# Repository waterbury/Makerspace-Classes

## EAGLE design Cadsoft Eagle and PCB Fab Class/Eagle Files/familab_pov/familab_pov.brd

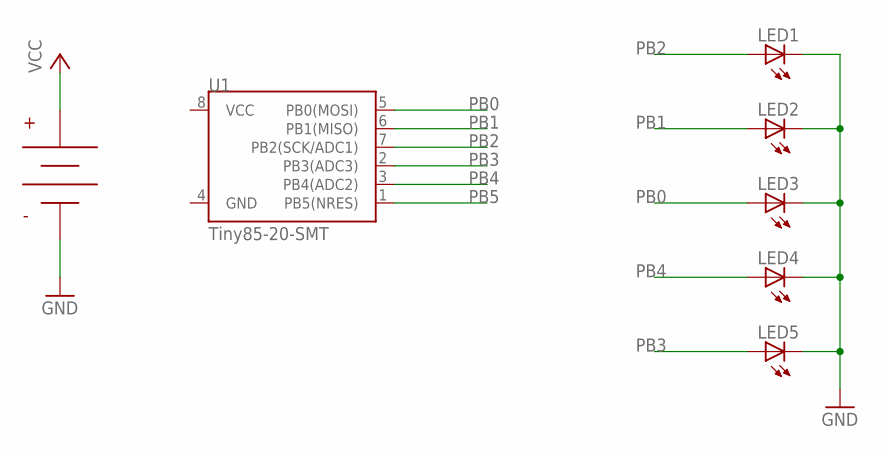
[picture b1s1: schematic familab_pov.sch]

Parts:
LED1, LED2, LED3, LED4, LED5: LED; LED5MM_SMD_SIDE
U1: Tiny85-20-SMT; SO08-EIAJ
U$1: CR2032_HOLDER; CR2032_BC2032-F1

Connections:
GND: LED1.C, LED2.C, LED3.C, LED4.C, LED5.C, U$1.NEG
PB0: LED3.A, U1.5 (PB0(MOSI))
PB1: LED2.A, U1.6 (PB1(MISO))
PB2: LED1.A, U1.7 (PB2(SCK/ADC1))
PB3: LED5.A, U1.2 (PB3(ADC3))
PB4: LED4.A, U1.3 (PB4(ADC2))
PB5: U1.1 (PB5(NRES))
VCC: U$1.POS

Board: 2 copper layers, 7 parts (0 on the bottom side), 6 nets, no tracks yet.

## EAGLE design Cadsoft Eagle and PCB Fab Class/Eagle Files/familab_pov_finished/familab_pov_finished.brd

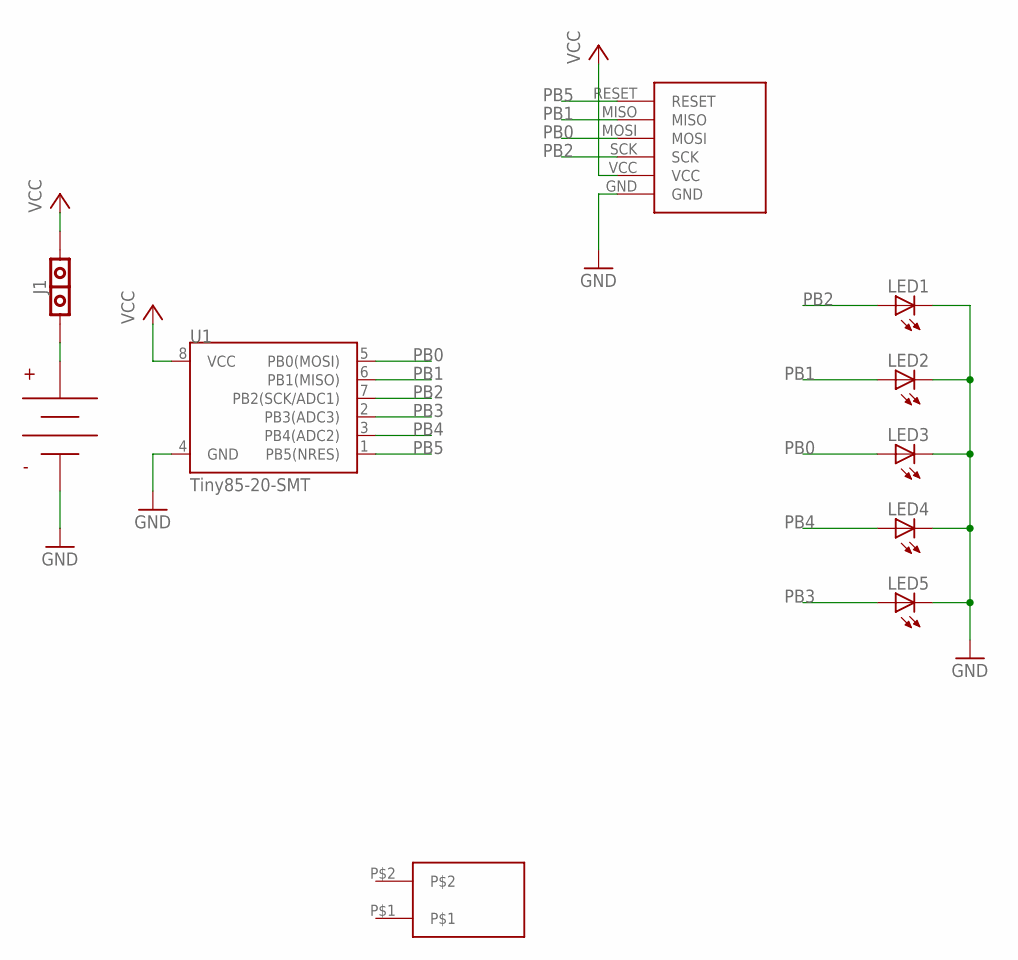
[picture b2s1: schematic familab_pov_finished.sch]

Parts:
J1: JUMPERSIDE; JUMPER_SMD_SIDE
LED1, LED2, LED3, LED4, LED5: LEDLED_5MM_SMD_SIDE; LED5MM_SMD_SIDE
U1: Tiny85-20-SMT; SO08-EIAJ
U$1: CR2032_HOLDER; CR2032_BC2032-F1
U$2: MOUNTING_PAD; MOUNTING_PADS
U$4: ICSP_PROGRAM; POV_ISP_CONNECTOR

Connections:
GND: LED1.CATHODE (C), LED2.CATHODE (C), LED3.CATHODE (C), LED4.CATHODE (C), LED5.CATHODE (C), U1.4 (GND), U$1.NEG, U$4.GND
unnamed: J1.P$1, U$1.POS
PB0: LED3.ANODE (A), U1.5 (PB0(MOSI)), U$4.MOSI
PB1: LED2.ANODE (A), U1.6 (PB1(MISO)), U$4.MISO
PB2: LED1.ANODE (A), U1.7 (PB2(SCK/ADC1)), U$4.SCK
PB3: LED5.ANODE (A), U1.2 (PB3(ADC3))
PB4: LED4.ANODE (A), U1.3 (PB4(ADC2))
PB5: U1.1 (PB5(NRES)), U$4.RESET
VCC: J1.P$2, U1.8 (VCC), U$4.VCC

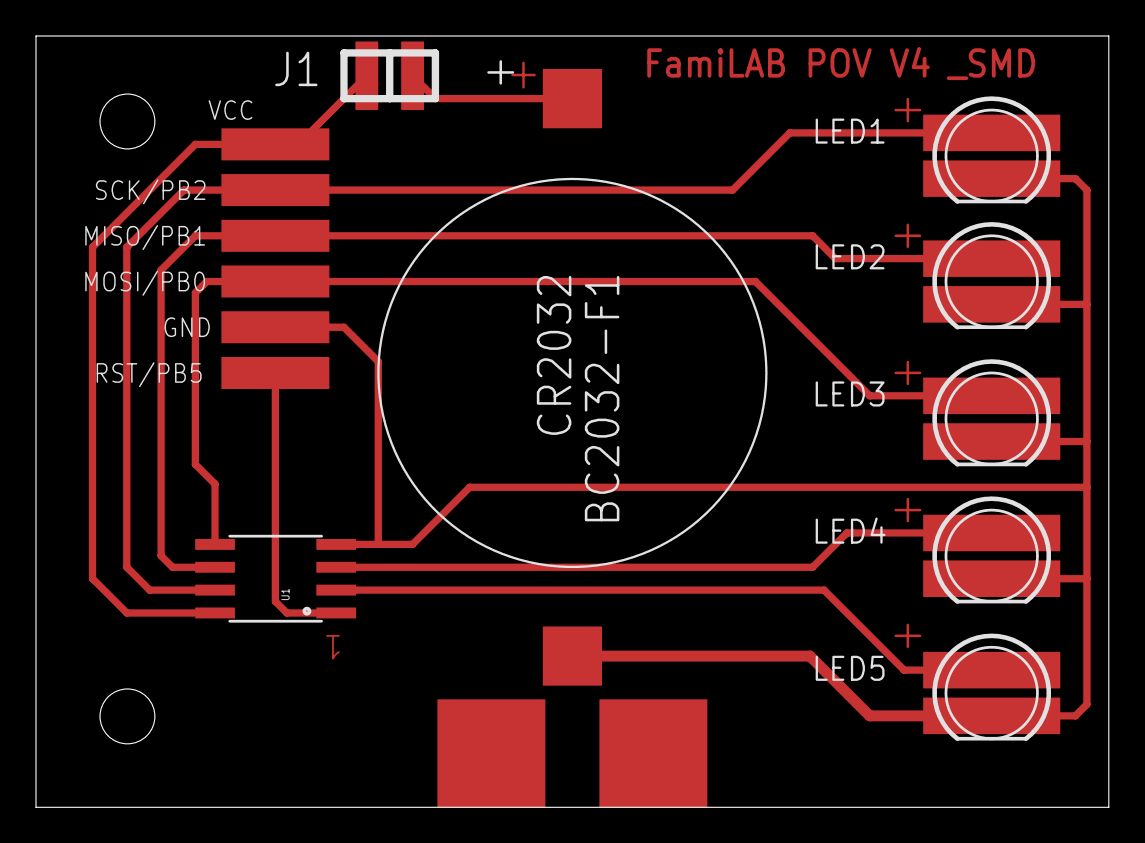
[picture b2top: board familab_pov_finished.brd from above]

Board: 2 copper layers, 59.6 x 42.9 mm, 10 parts (0 on the bottom side), 9 nets.

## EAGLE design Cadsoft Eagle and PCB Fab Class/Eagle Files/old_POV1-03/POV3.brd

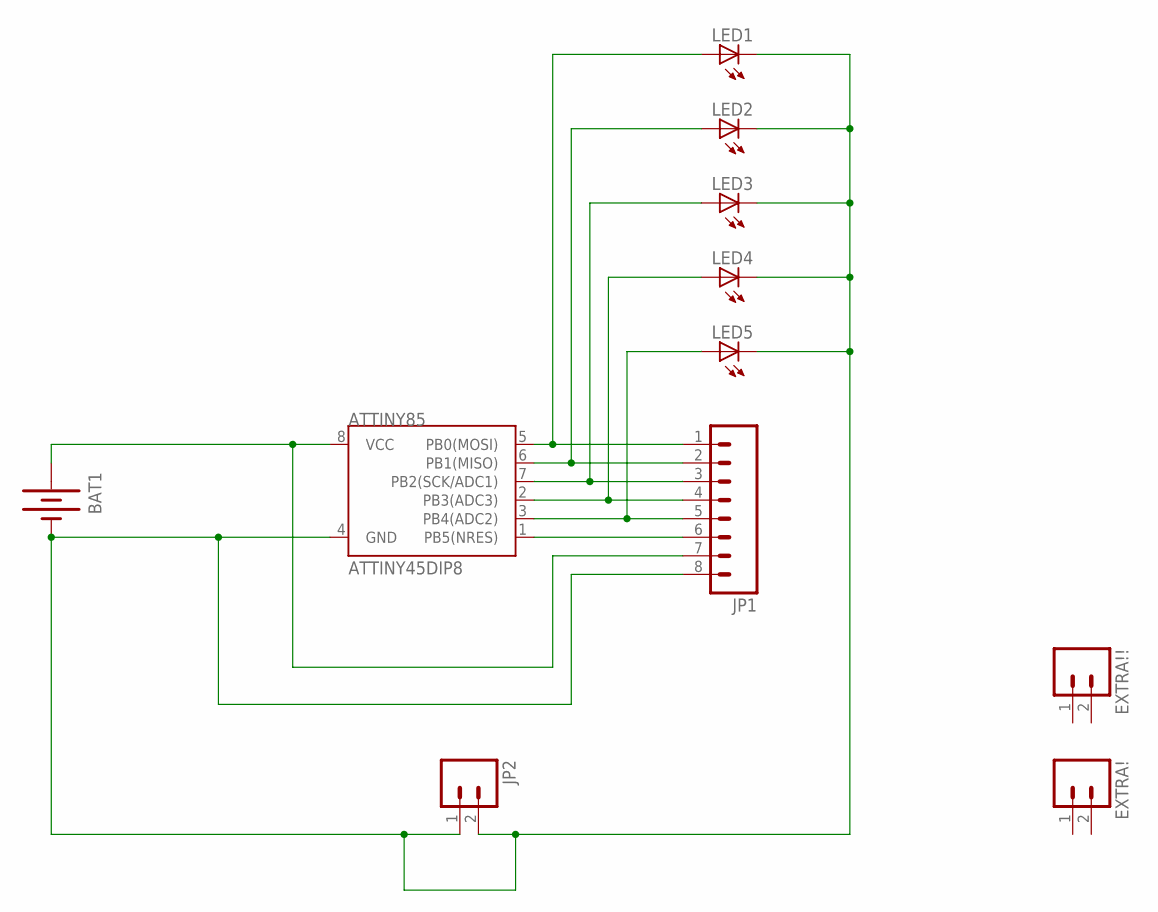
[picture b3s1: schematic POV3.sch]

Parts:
ATTINY85: ATTINY45DIP8; DIP08
BAT1: BATTERY20PTH; BATTCOM_20MM_PTH
EXTRA!: M02PTH; 1X02
EXTRA!!: M02PTH; 1X02
JP1: M08; 1X08
JP2: M02PTH; 1X02
LED1, LED2, LED3, LED4, LED5: LED5MM

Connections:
unnamed: ATTINY85.8 (VCC), BAT1.1 (+), JP1.7
unnamed: ATTINY85.5 (PB0(MOSI)), JP1.1, LED1.A
unnamed: ATTINY85.6 (PB1(MISO)), JP1.2, LED2.A
unnamed: ATTINY85.7 (PB2(SCK/ADC1)), JP1.3, LED3.A
unnamed: ATTINY85.2 (PB3(ADC3)), JP1.4, LED4.A
unnamed: ATTINY85.3 (PB4(ADC2)), JP1.5, LED5.A
unnamed: ATTINY85.1 (PB5(NRES)), JP1.6
unnamed: ATTINY85.4 (GND), BAT1.2 (-), JP1.8, JP2.1, JP2.2, LED1.K (C), LED2.K (C), LED3.K (C), LED4.K (C), LED5.K (C)

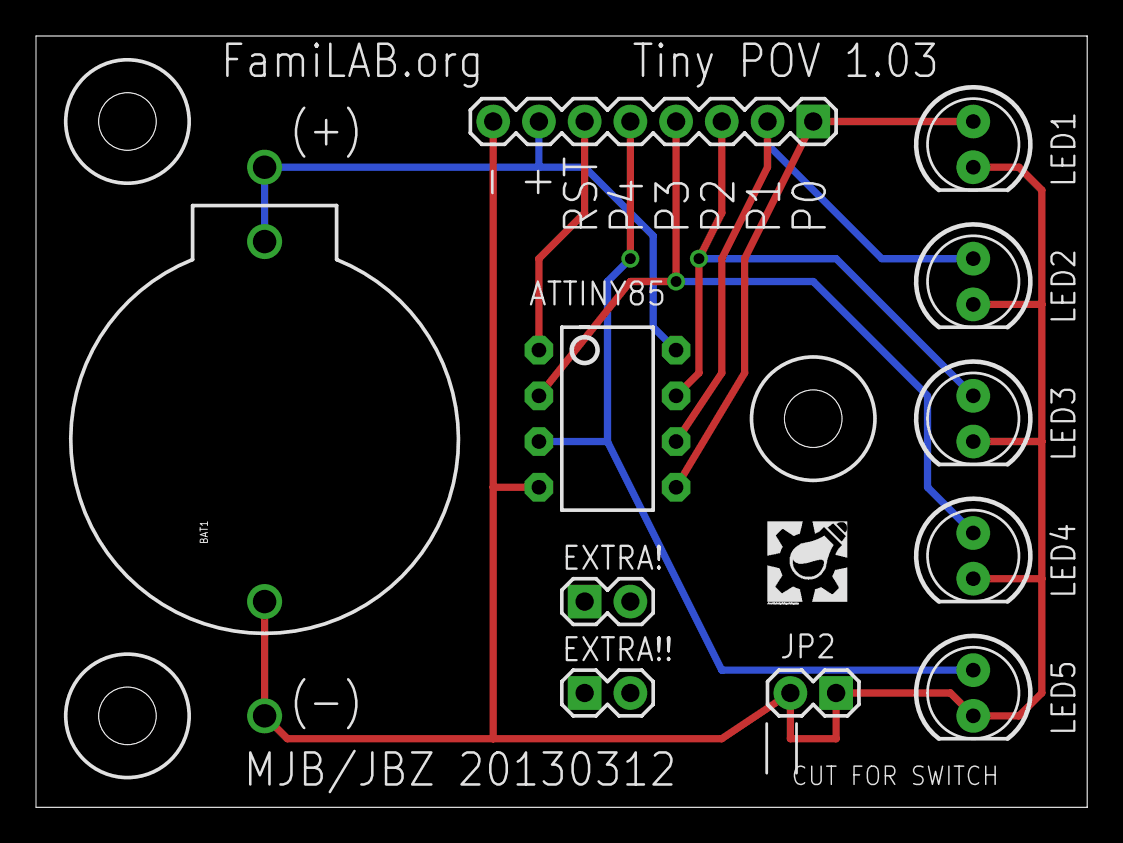
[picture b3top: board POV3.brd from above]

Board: 2 copper layers, 58.4 x 42.9 mm, 15 parts (0 on the bottom side), 8 nets.

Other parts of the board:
U$1: FAMILAB
U$2, U$3, U$4: 3,2

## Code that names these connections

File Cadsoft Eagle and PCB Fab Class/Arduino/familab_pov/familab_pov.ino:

/*
 *  TinyPOV - program an ATTiny85 to do persistance of vision
 *
 *  20130403  MJB  Initial version. (Michael J Bakula)
 *  20130405  MJB  General clean up.
 */


//Defines


#define ASCII_OFFSET 97


// Global Variables

int columnsDrawn = 0;
int columnsPerRotation = 50;
char newSymbol[5] = {0,0,0,0,0};
// message to be displayed -- only 'a-z' for now.
char message[] = "abc     ";


byte colTime = 1;  //ms
byte chrTime = 3;


byte msgLen;
byte symLen = 5;


// symbol[] contains the bit codes for the letters
// to be displayed, 5 bytes per letter.
byte symbol[] = {
   1,  6, 26,  6,  1,  // a
  31, 21, 21, 10,  0,  // b
  14, 17, 17, 10,  0,  // c
  31, 17, 17, 14,  0,  // d
  31, 21, 21, 17,  0,  // e
  31, 20, 20, 16,  0,  // f
  14, 17, 19, 10,  0,  // g
  31,  4,  4,  4, 31,  // h
   0, 17, 31, 17,  0,  // i
   0, 17, 30, 16,  0,  // j
  31,  4, 10, 17,  0,  // k
  31,  1,  1,  1,  0,  // l
  31, 12,  3, 12, 31,  // m
  31, 12,  3, 31,  0,  // n
  14, 17, 17, 14,  0,  // o
  31, 20, 20,  8,  0,  // p
  14, 17, 19, 14,  2,  // q
  31, 20, 22,  9,  0,  // r
   8, 21, 21,  2,  0,  // s
  16, 16, 31, 16, 16,  // t
  30,  1,  1, 30,  0,  // u
  24,  6,  1,  6, 24,  // v
  28,  3, 12,  3, 28,  // w
  17, 10,  4, 10, 17,  // x
  17, 10,  4,  8, 16,  // y
  19, 21, 21, 25,  0,  // z
};


void setup() {
  DDRB = 0x1F;  // set the LED pins to OUTPUT
  msgLen = strlen(message);
} // setup()


void loop() {
  
  columnsDrawn = 0;
  for (byte i=0; i<msgLen  && (columnsDrawn < columnsPerRotation ); i++) {
    
    if (message[i] >= 97 && message[i] <=122){
      newSymbol[0] =  ledTransform( symbol[(message[i]-ASCII_OFFSET) *symLen +0]  );
      newSymbol[1] =  ledTransform( symbol[(message[i]-ASCII_OFFSET) *symLen +1]  );
      newSymbol[2] =  ledTransform( symbol[(message[i]-ASCII_OFFSET) *symLen +2]  );
      newSymbol[3] =  ledTransform( symbol[(message[i]-ASCII_OFFSET) *symLen +3]  );
      newSymbol[4] =  ledTransform( symbol[(message[i]-ASCII_OFFSET) *symLen +4]  );
    }
   else{
      newSymbol[0] = 0;
      newSymbol[1] = 0;
      newSymbol[2] = 0;
      newSymbol[3] = 0;
      newSymbol[4] = 0;
     
     
   }
   
    
    for (byte j=0; j<symLen && (columnsDrawn < columnsPerRotation ); j++) {
      // assign the symbol table column to the LEDs
      PORTB = newSymbol[j];
      delay(colTime);
      columnsDrawn++;
    }
    delay(chrTime);
  }
} // loop()


byte ledTransform(byte oldLED){
  byte newLED = 0;
  
 if (oldLED & 0x10) //LED 1
  newLED += 0x4; //LED is now at PB2
 if (oldLED & 0x8) //LED 2
  newLED += 0x2; //LED is still at PB1
 if (oldLED & 0x4) //LED 3
  newLED += 0x1; //LED is now at PB0 
 if (oldLED & 0x2) //LED 4
  newLED += 0x10; //LED is now at PB4   
 if (oldLED & 0x1) //LED 5
  newLED += 0x8; //LED is now at PB3 
 
 
 
return newLED;
}

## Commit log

2014-10-10 :confetti_ball: Added .gitattributes & .gitignore files
2014-11-12 Increased Dimensions slightly and Fixed Arduino Code
2014-11-12 Added Arduino 102 Class Slides

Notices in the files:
parts and their libraries:
SparkFun-DigitalIC: Licensing: Creative Commons ShareAlike 4.0 International - https://creativecommons.org/licenses/by-sa/4.0
SparkFun: Licensing: CC v3.0 Share-Alike You are welcome to use this library for commercial purposes.
